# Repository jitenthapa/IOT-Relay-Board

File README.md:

# IOT-Relay-Board
Generic IOT Board with two 12V Relay System

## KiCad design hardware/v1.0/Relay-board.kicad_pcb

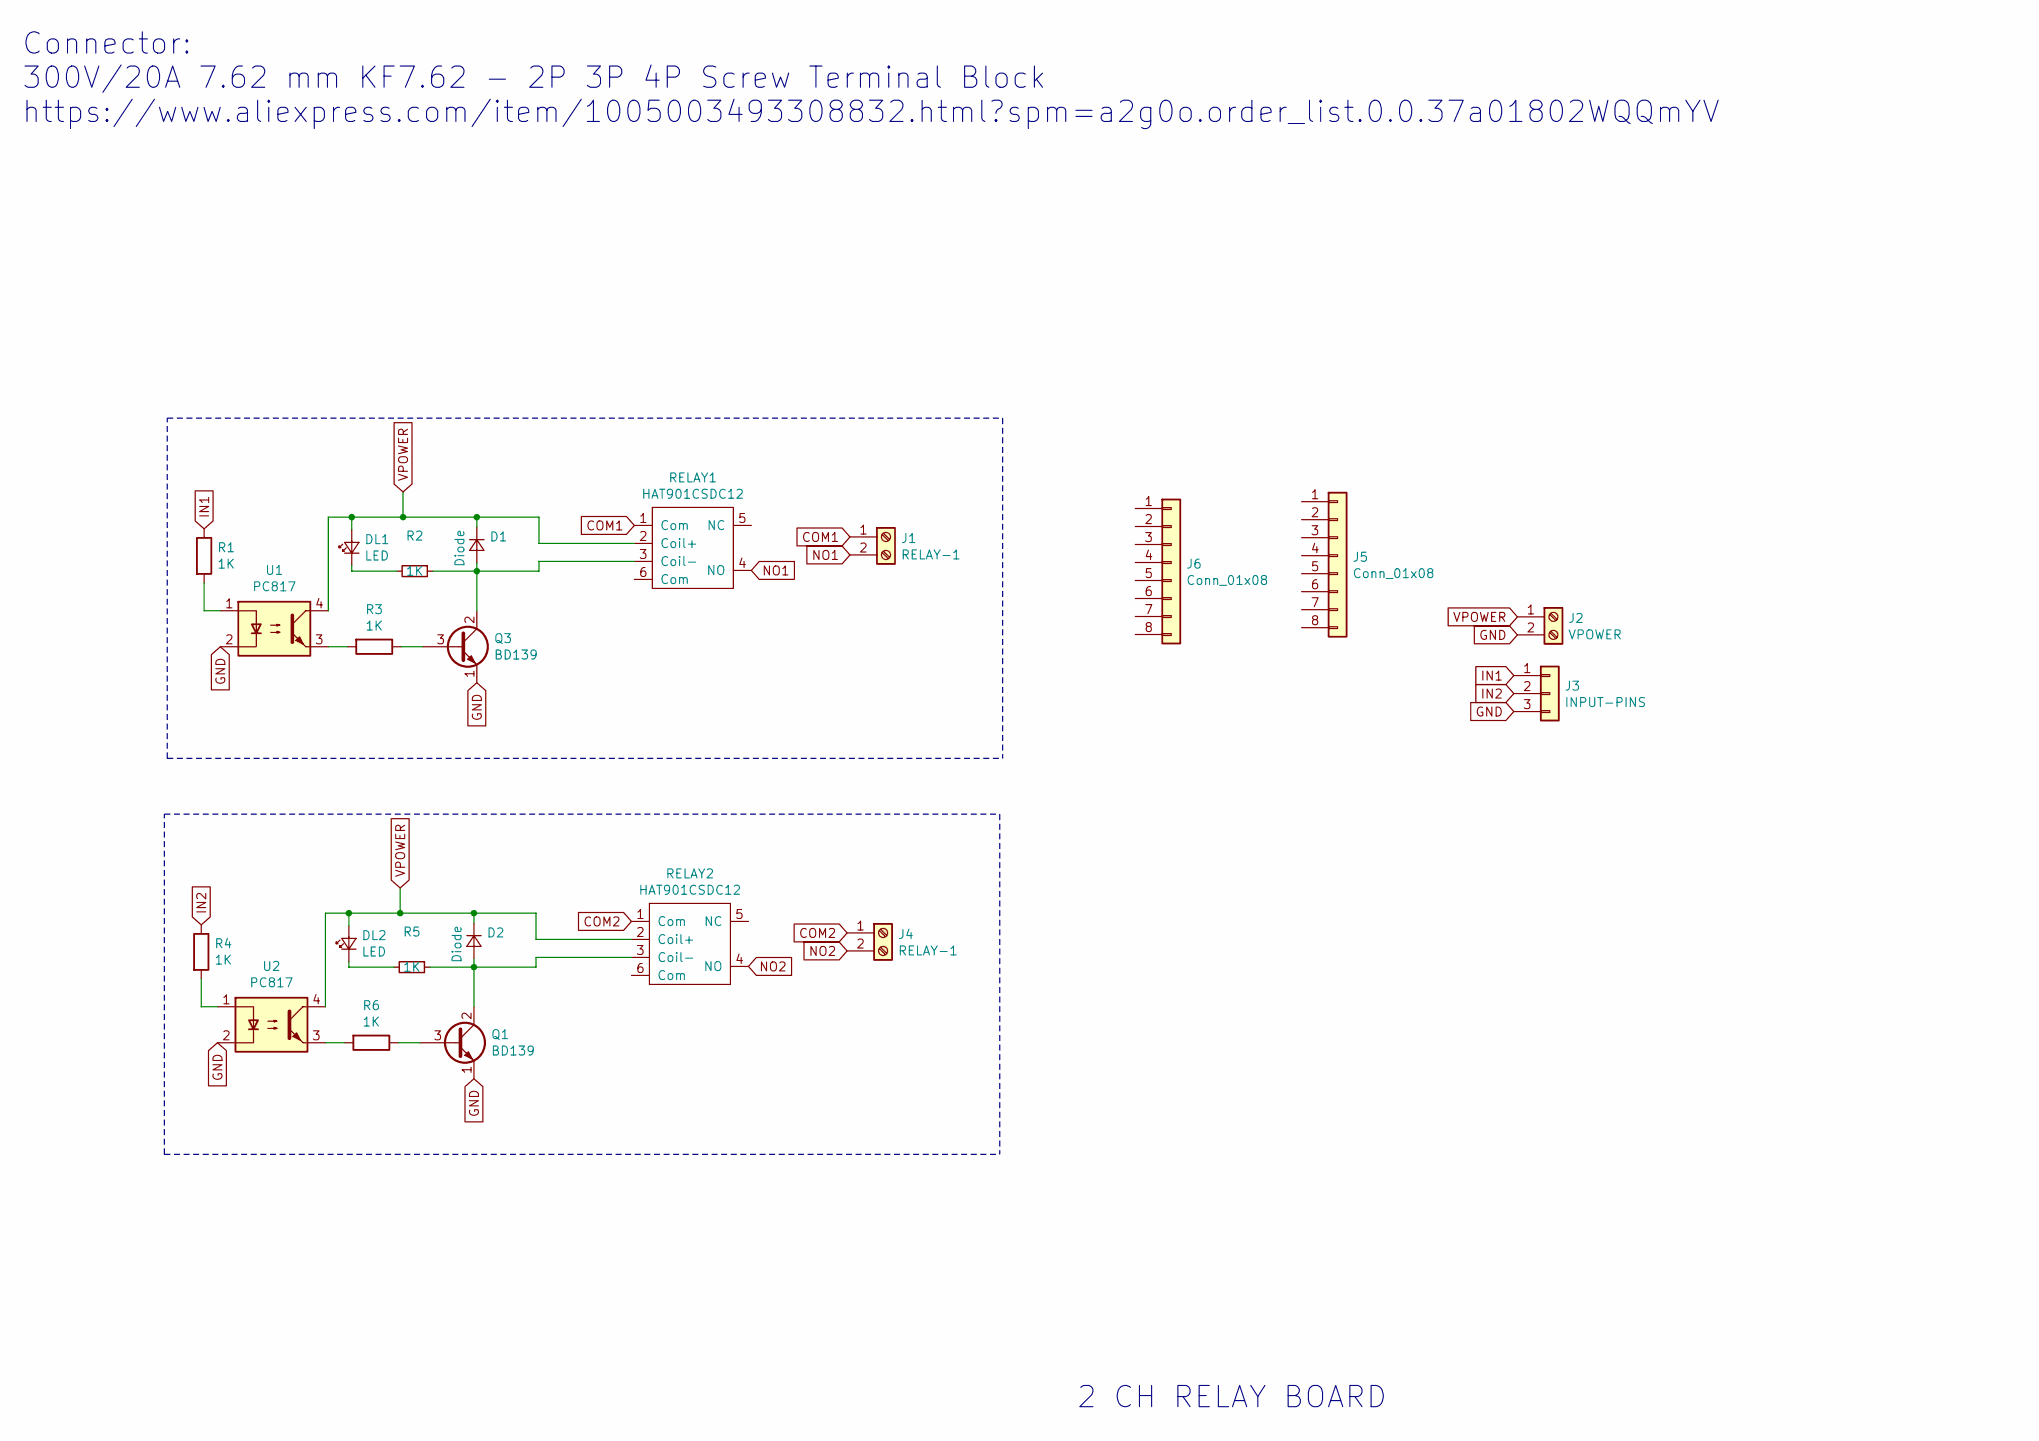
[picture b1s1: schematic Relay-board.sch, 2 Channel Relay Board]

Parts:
D1, D2: Diode; SMA-DO214AC
DL1, DL2: LED; LED_0805_2012Metric
J1, J4: RELAY-1; dual terminal-small-4
J2: VPOWER; dual terminal-small-4
J3: INPUT-PINS; PinHeader_1x03_P2.54mm_Vertical
J5, J6: Conn_01x08; PinHeader_1x08_P2.54mm_Vertical
Q1, Q3: BD139; TO-251-3_Vertical
R1, R2, R3, R4, R5, R6: 1K; R_0805_2012Metric
RELAY1, RELAY2: HAT901CSDC12; HAT901CSDC12-large-holes
U1, U2: PC817; SOT254P1025X400-4N

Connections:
COM1: J1.1, RELAY1.1 (Com)
COM2: J4.1, RELAY2.1 (Com)
GND: J2.2, J3.3, Q1.1 (E), Q3.1 (E), U1.2, U2.2
IN1: J3.1, R1.1
IN2: J3.2, R4.1
NO1: J1.2, RELAY1.4 (NO)
NO2: J4.2, RELAY2.4 (NO)
unnamed: D1.2 (A), Q3.2 (C), R2.1, RELAY1.3 (Coil-)
unnamed: D2.2 (A), Q1.2 (C), R5.1, RELAY2.3 (Coil-)
unnamed: DL1.1 (K), R2.2
unnamed: DL2.1 (K), R5.2
unnamed: Q1.3 (B), R6.1
unnamed: Q3.3 (B), R3.1
unnamed: R1.2, U1.1
unnamed: R3.2, U1.3
unnamed: R4.2, U2.1
unnamed: R6.2, U2.3
VPOWER: D1.1 (K), D2.1 (K), DL1.2 (A), DL2.2 (A), J2.1, RELAY1.2 (Coil+), RELAY2.2 (Coil+), U1.4, U2.4

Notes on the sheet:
2 CH RELAY BOARD
Connector: 300V/20A 7.62 mm KF7.62 - 2P 3P 4P Screw Terminal Block https://www.aliexpress.com/item/1005003493308832.html?spm=a2g0o.order_list.0.0.37a01802WQQmYV

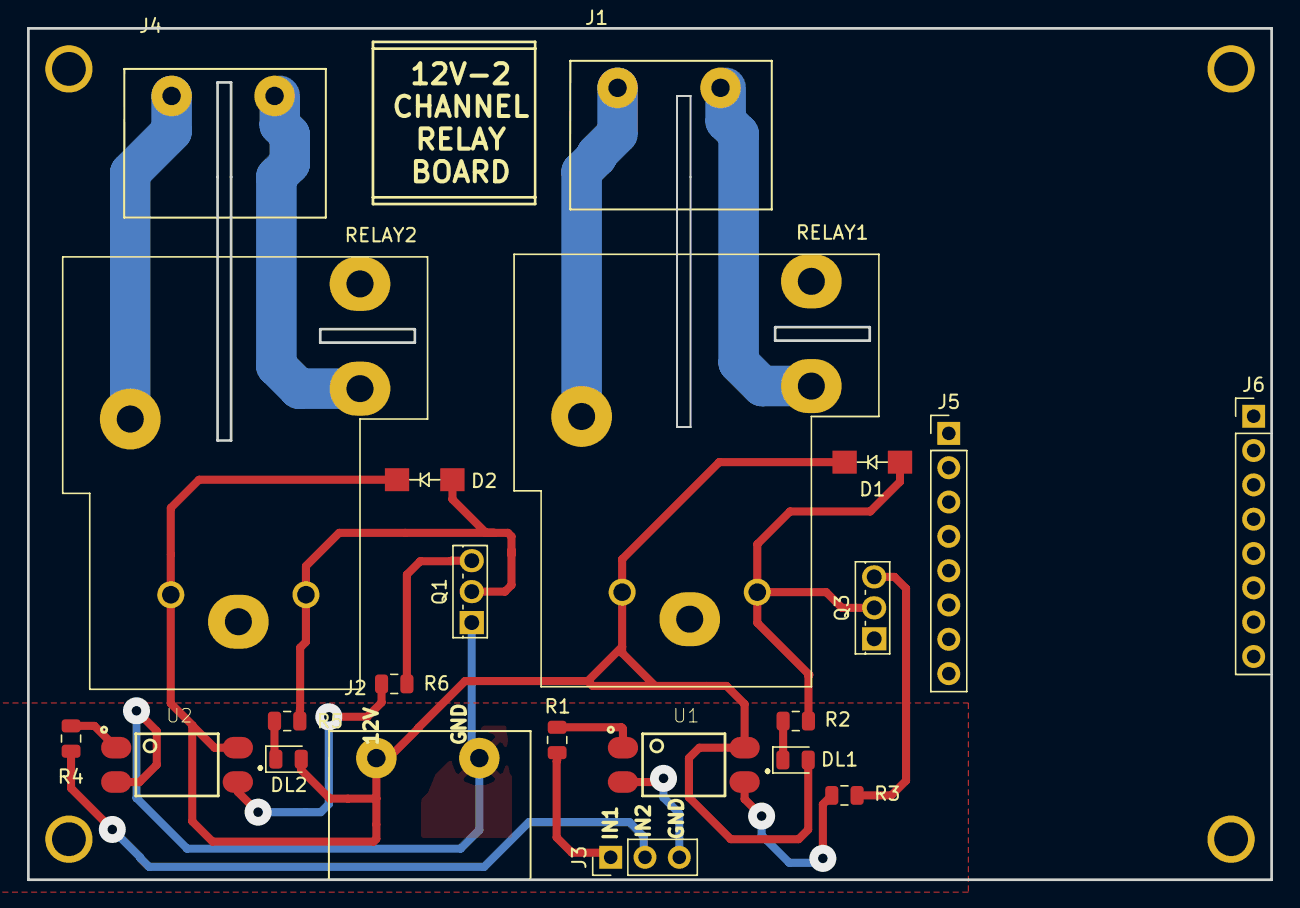
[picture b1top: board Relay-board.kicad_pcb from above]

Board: 2 copper layers, 92.0 x 63.0 mm, 26 parts (0 on the bottom side), 18 nets.

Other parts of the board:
MH1, MH2, MH3, MH4: MountingHole_2.5mm
